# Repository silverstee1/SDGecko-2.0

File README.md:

# SDGecko-2.0
MicroSD Card Adapter For GameCube's Front Memcard Slots v2.0

Based on the SD2SP2 2.0 made by Extrems, Thank you for your hard work!

***Important Note about Old Gerbers/Worn out SD Card Issues***

Previous version of gerbers could cause 3v3 short to GND by some sus SD card models that have worn out edges exposing 3v3 plane to CD pin when inserted, this is fixed in new gerbers by making the SD card slot GND shield floating to prevent the issue regardless of the card being worn out.

One solution for old gerbers is to snip off the GND shield that the CD switch engages when a card is inserted to prevent old worn SD card edges from shorting to GND as shown in the image below.

**Important**

When using the adapter make sure to have the Latest Version of Swiss, Due to the way Swiss handles it in SLOT A it 
acts like a normal speed Passive SDGecko, in SLOT B it works in Semi-Passive 2.0 enhanced speed mode.

https://github.com/emukidid/swiss-gc

SDGecko+2.0 BOM
=====================================
The PCB must be ordered (e.g. from jlcpcb) in 1.6mm thickness with surface finish ENIG at minimum.

**3D Printed Case Enclosure**

You'll need to 3D print the case enclosure Top and Bottom pieces from the Case folder to use it in your Memcard Slot preferably on an FDM printer, 
the case screws are countersunk self tapping M2x5 screws.

**Note**

R1,R2,D1,D2 are not necessary if you don't want to have LED's in your adapter or want to minimize on components.

**SDGecko2.0+ PCB**

**C1:** 0402 22u Capactior (10V Min) - DigiKey Part# 490-GRM158R61A226ME15DCT-ND

LCSC Part# C3845593

**R1:** 0402 14ohm Resistor - Digikey Part# P14.0LCT-ND

LCSC Part# C400609

**R2:** 0402 14ohm Resistor - Digikey Part# P14.0LCT-ND

LCSC Part# C400609

**D1:** 0402 Green Led 20ma (Dot on PCB footprint marks LED Cathode side) - Digikey Part# 1516-1216-1-ND

LCSC Part# C2856703

**D2:** 0402 Blue Led 20ma (Dot on PCB footprint marks LED Cathode side) - Digikey Part# 1516-1215-1-ND

LCSC Part # C965797

**J4:** MicroSD Slot - DigiKey Part# 2223-MSD-4-ACT-ND

LCSC Part# C113206

**U1:** OR Gate IC - DigiKey Part# 296-1093-1-ND

LCSC Part# C7470

Alt Nexperia Digikey Part# 1727-3067-1-ND

LCSC Alt Nexperia Part# C12488

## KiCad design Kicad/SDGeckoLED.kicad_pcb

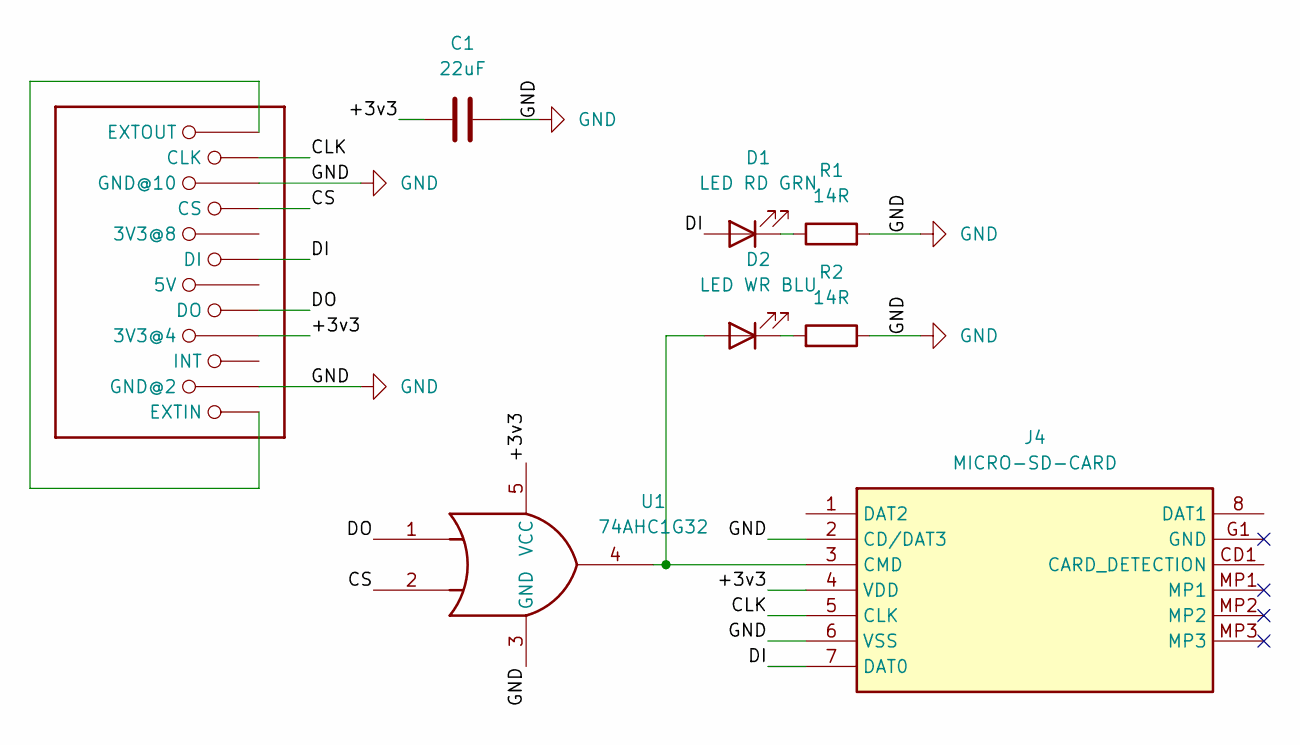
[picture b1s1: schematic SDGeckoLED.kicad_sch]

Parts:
C1: 22uF; C_0402_1005Metric_Pad0.74x0.62mm_HandSolder; LCSC PN C3845593
D1: LED RD GRN; LED_0402_1005Metric_Pad0.77x0.64mm_HandSolder; LCSC PN C2856703
D2: LED WR BLU; LED_0402_1005Metric_Pad0.77x0.64mm_HandSolder; LCSC PN C965797
J2: GC_MEMCARD
J4: MICRO-SD-CARD; MICROSDCARD; Mouser Part Number 909-MICRO-SD-CARD
R1, R2: 14R; R_0402_1005Metric_Pad0.72x0.64mm_HandSolder; LCSC PN C400609
U1: 74AHC1G32; SC-74A-5_1.55x2.9mm_P0.95mm; LCSC PN C12488

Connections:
/+3v3: C1.1, J2.4 (3V3@4), J4.4 (VDD), U1.5 (VCC)
/CLK: J2.11 (CLK), J4.5 (CLK)
/CS: J2.9 (CS), U1.2
/DI: D1.2 (A), J2.7 (DI), J4.7 (DAT0)
/DO: J2.5 (DO), U1.1
GND: C1.2, J2.2 (GND@2), J2.10 (GND@10), J4.2 (CD/DAT3), J4.6 (VSS), R1.2, R2.1, U1.3 (GND)
unnamed: D1.1 (K), R1.1
unnamed: D2.2 (A), J4.3 (CMD), U1.4
unnamed: D2.1 (K), R2.2
unnamed: J2.1 (EXTIN), J2.12 (EXTOUT)

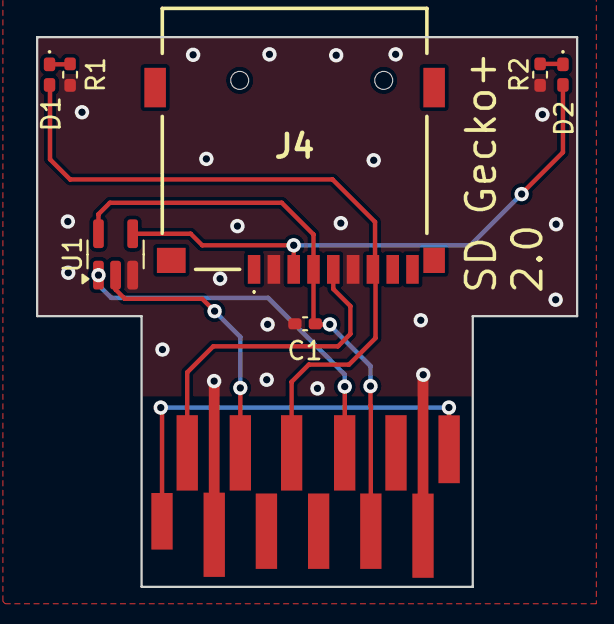
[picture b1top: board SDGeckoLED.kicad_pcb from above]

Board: 2 copper layers, 30.0 x 30.5 mm, 8 parts (0 on the bottom side), 10 nets.

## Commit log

2024-06-29 project upload
2025-09-04 Delete PCB Gerbers/SDGecko+2.0_Gerbers.zip
    removing old gerbers to prevent issues with some models of SD cards that when SD card edge near CD pin wears out soldermask short 3v3 card edge to CD pin / GND.
2025-09-04 fixes for sus worn out SD cards
    leaves Micro SD card shield floating to prevent worn out solder mask exposing 3v3 edge to CD pin and shorting to GND
2025-09-04 updated kicad project for sd gerber fix
2025-09-04 Update README.md
    Info out changes and old gerber solutions
